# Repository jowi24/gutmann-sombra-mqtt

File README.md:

🇬🇧 **English** · 🇩🇪 [Deutsch](README.de.md)

# gutmann-sombra-mqtt

An ESP8266 board that connects a Gutmann Sombra range hood (cooker hood) to
home automation over Wi-Fi and MQTT, with Home Assistant auto-discovery.
The board sits in the cable between the hood electronics and the front
panel. It reads which front-panel LEDs are lit and can simulate key presses.
The original front panel keeps working as before.

- **Hardware:** KiCad 10 PCB, 80 × 55 mm, through-hole except the ESP-12E
  module, fabrication files included
- **Firmware:** PlatformIO / Arduino, MQTT with Home Assistant discovery,
  OTA updates, Wi-Fi setup portal

## Documentation

| Document | Contents |
|---|---|
| [How the circuit works](docs/CIRCUIT.md) | Beginner-friendly explanation of the hardware: the hood's key matrix, level shifters, power supply, firmware timing, troubleshooting |
| [Hardware design notes](kicad/DESIGN.md) | Part values, sourcing, layout decisions, bring-up findings |
| [Fabrication files](kicad/fab/FAB.md) | Gerber/drill files and PCB order parameters |
| [Operation, diagnostics and flashing](docs/OPERATIONS.md) | Setup, OTA and serial flashing, diagnostics |
| [Changelog](CHANGELOG.md) | Firmware versions |

All documents are also available in German (`*.de.md`).

## Status

- **Hardware:** PCB rev. 0.3, see the [schematic](kicad/schematic.pdf) and
  the [layout](kicad/board-layout.pdf). The fabricated rev. 0.2 boards work
  after a small modification at U3 (diodes + pull-downs, see
  [DESIGN.md](kicad/DESIGN.md)).
- **Firmware:** 0.0.10, PlatformIO, source in [`src/main.cpp`](src/main.cpp).

## Project layout

```
src/main.cpp          firmware
platformio.ini        build configuration (serial and OTA flashing)
docs/                 operation and circuit description
kicad/                schematic, PCB, custom footprint and 3D model
kicad/fab/            fabrication files
fritzing/             2017 perfboard version (reference only)
```

## Building and flashing the firmware

```bash
pio run -e nodemcuv2-ota -t upload
```

This flashes over Wi-Fi (OTA) to `hood-control.local`. For the first flash
or for recovery, use `-e nodemcuv2` via a USB-serial adapter on J2, with
jumper J5 set to FLASH. Details in [OPERATIONS.md](docs/OPERATIONS.md).

## MQTT

All topics live under the configured prefix (default `home/kitchen/hood`).
Home Assistant picks the device up automatically via MQTT discovery
(`homeassistant/…`).

| Topic | Values | Meaning |
|---|---|---|
| `ventilation/state`, `ventilation/set` | `0`–`4` | fan level, `0` = off |
| `light/state`, `light/set` | `true` / `false` | light |
| `timer/state`, `timer/set` | `true` / `false` | run-on timer |
| `maintenance/state` | `true` / `false` | "clean filter" indicator |
| `maintenance/set` | any | resets the filter indicator (6 s key press, only while it is on) |

Diagnostics:

- `diagnostics`: combined JSON status
- `$wifi_rssi`, `$uptime`, `$reset_reason`, `$firmware`, `$ip`, `$last_error`
- `events`: connection events buffered since the last MQTT contact
- `$online`: availability via MQTT last will

## Network

If the stored Wi-Fi network cannot be reached for 20 seconds, the firmware
starts the password-protected hotspot `HoodControl-Setup`. The setup portal
is at `http://192.168.4.1`. The device keeps trying the stored network in
parallel and shuts the hotspot down once the connection is stable.

The blue LED on the ESP module shows the state: fast blinking = connecting
to Wi-Fi, medium = connecting to MQTT, slow = hotspot active, a short flash
every 3 s = all good.

## Background

Blog post about the original 2017 perfboard version (German):
[Do-It-Yourself IoT Modul für die Dunstabzugshaube](https://joachim-wilke.de/blog/2017/12/27/do-it-yourself-iot-modul-fur-die-dunstabzugshaube/)

## License

Copyright (c) 2017–2026 Joachim Wilke. The firmware is open source (MIT). Hardware
and documentation are free for **non-commercial** use only; commercial use (e.g. selling boards, kits or products based on this project)
requires the author's permission.

- **Firmware** (`src/`, `platformio.ini`): [MIT](LICENSE)
- **Hardware and documentation** (`kicad/`, `fritzing/`, `docs/`, Markdown files):
  [CC BY-NC-SA 4.0](LICENSE-HARDWARE-DOCS)

Third-party libraries used by the firmware keep their own licenses.

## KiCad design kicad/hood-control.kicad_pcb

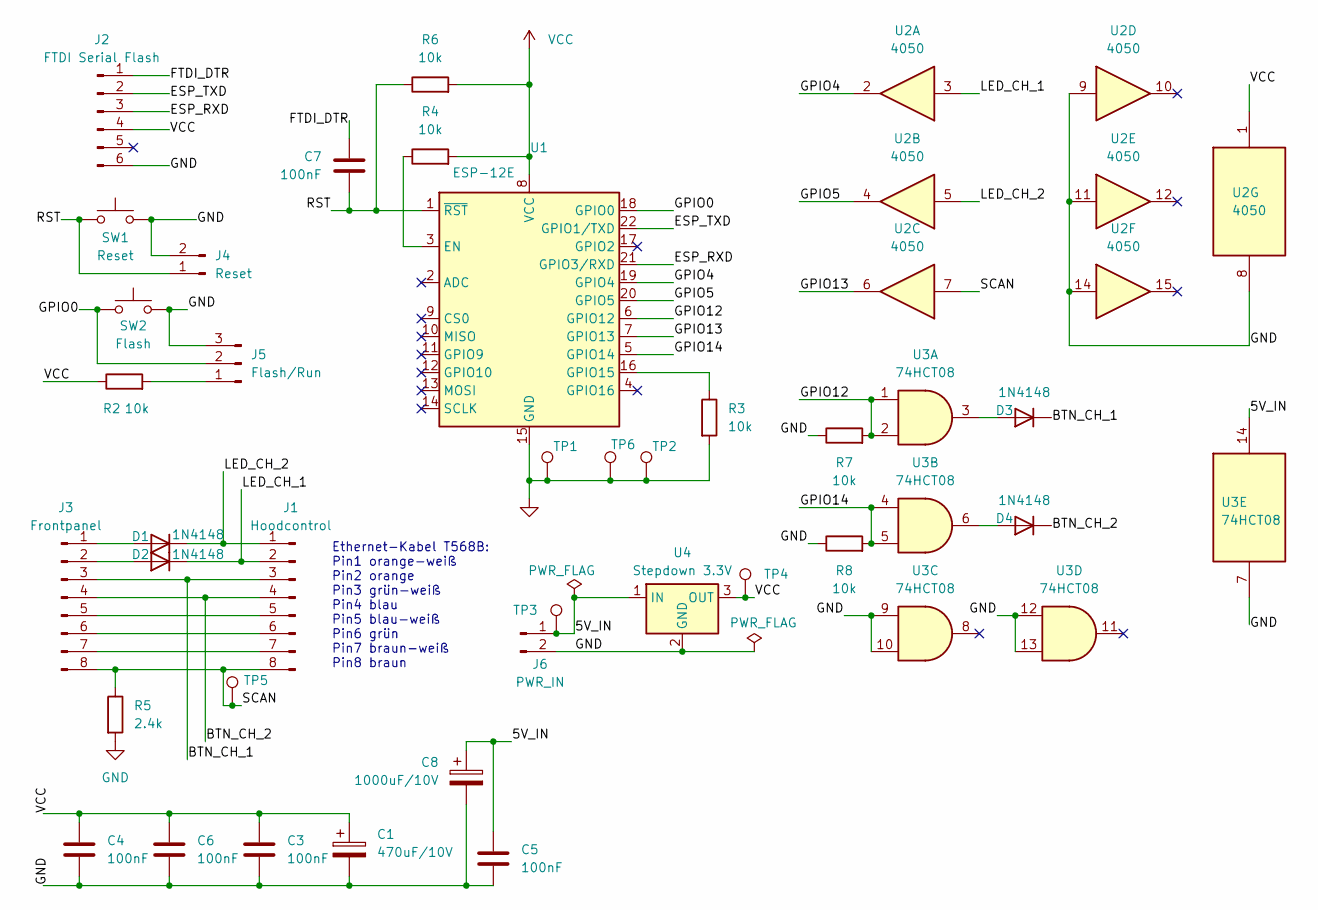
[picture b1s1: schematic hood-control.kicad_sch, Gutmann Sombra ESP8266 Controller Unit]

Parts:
C1: 470uF/10V; CP_Radial_D8.0mm_P3.50mm
C3, C4, C5, C6, C7: 100nF; C_Disc_D5.0mm_W2.5mm_P5.00mm
C8: 1000uF/10V; CP_Radial_D10.0mm_P5.00mm
D1, D2: 1N4148; D_DO-35_SOD27_P7.62mm_Horizontal
D3, D4: 1N4148; D_DO-35_SOD27_P2.54mm_Vertical_AnodeUp
J1: Hoodcontrol; PinHeader_1x08_P2.54mm_Vertical
J2: FTDI Serial Flash; PinHeader_1x06_P2.54mm_Vertical
J3: Frontpanel; PinHeader_1x08_P2.54mm_Vertical
J4: Reset; PinHeader_1x02_P2.54mm_Vertical
J5: Flash/Run; PinHeader_1x03_P2.54mm_Vertical
J6: PWR_IN; PinHeader_1x02_P2.54mm_Vertical
R2, R3, R4, R6: 10k; R_Axial_DIN0207_L6.3mm_D2.5mm_P10.16mm_Horizontal
R5: 2.4k; R_Axial_DIN0207_L6.3mm_D2.5mm_P10.16mm_Horizontal
R7, R8: 10k; R_Axial_DIN0207_L6.3mm_D2.5mm_P2.54mm_Vertical
SW1: Reset; SW_PUSH_6mm
SW2: Flash; SW_PUSH_6mm
TP1, TP2, TP6: GND; TestPoint_THTPad_1.5x1.5mm_Drill0.7mm
TP3: 5V; TestPoint_THTPad_1.5x1.5mm_Drill0.7mm
TP4: 3.3V; TestPoint_THTPad_1.5x1.5mm_Drill0.7mm
TP5: SCAN; TestPoint_THTPad_1.5x1.5mm_Drill0.7mm
U1: ESP-12E
U2: 4050; DIP-16_W7.62mm_Socket
U3: 74HCT08; DIP-14_W7.62mm_Socket
U4: Stepdown 3.3V; TPS63802_Module_25.8x13.0mm

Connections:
/5V_IN: C5.1, C8.1, J6.1, TP3.1 (1_1), U3.14 (VCC), U4.1 (IN)
/BTN_CH_1: D3.1 (K), J1.3, J3.3
/BTN_CH_2: D4.1 (K), J1.4, J3.4
/ESP_RXD: J2.3, U1.21 (GPIO3/RXD)
/ESP_TXD: J2.2, U1.22 (GPIO1/TXD)
/FTDI_DTR: C7.1, J2.1
/GPIO0: J5.2, SW2.1, U1.18 (GPIO0)
/GPIO4: U1.19 (GPIO4), U2.2
/GPIO5: U1.20 (GPIO5), U2.4
/GPIO12: R7.2, U1.6 (GPIO12), U3.1, U3.2
/GPIO13: U1.7 (GPIO13), U2.6
/GPIO14: R8.2, U1.5 (GPIO14), U3.4, U3.5
/LED_CH_1: D2.1 (K), J1.2, U2.3
/LED_CH_2: D1.1 (K), J1.1, U2.5
/RST: C7.2, J4.1, R6.1, SW1.1, U1.1 (~RST)
/SCAN: J1.8, J3.8, R5.1, TP5.1 (1_1), U2.7
GND: C1.2, C3.2, C4.2, C5.2, C6.2, C8.2, J2.6, J4.2, J5.3, J6.2, R3.2, R5.2, R7.1, R8.1, SW1.2, SW2.2, TP1.1 (1_1), TP2.1 (1_1), TP6.1 (1_1), U1.15 (GND), U2.8 (VSS), U2.9, U2.11, U2.14, U3.7 (GND), U3.9, U3.10, U3.12, U3.13, U4.2 (GND)
unnamed: D1.2 (A), J3.1
unnamed: D2.2 (A), J3.2
unnamed: D3.2 (A), U3.3
unnamed: D4.2 (A), U3.6
unnamed: J1.5, J3.5
unnamed: J1.6, J3.6
unnamed: J1.7, J3.7
unnamed: J5.1, R2.2
unnamed: R4.1, U1.3 (EN)
unnamed: R3.1, U1.16 (GPIO15)
VCC: C1.1, C3.1, C4.1, C6.1, J2.4, R2.1, R4.2, R6.2, TP4.1 (1_1), U1.8 (VCC), U2.1 (VCC), U4.3 (OUT)

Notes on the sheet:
Ethernet-Kabel T568B: Pin1 orange-weiß Pin2 orange Pin3 grün-weiß Pin4 blau Pin5 blau-weiß Pin6 grün Pin7 braun-weiß Pin8 braun

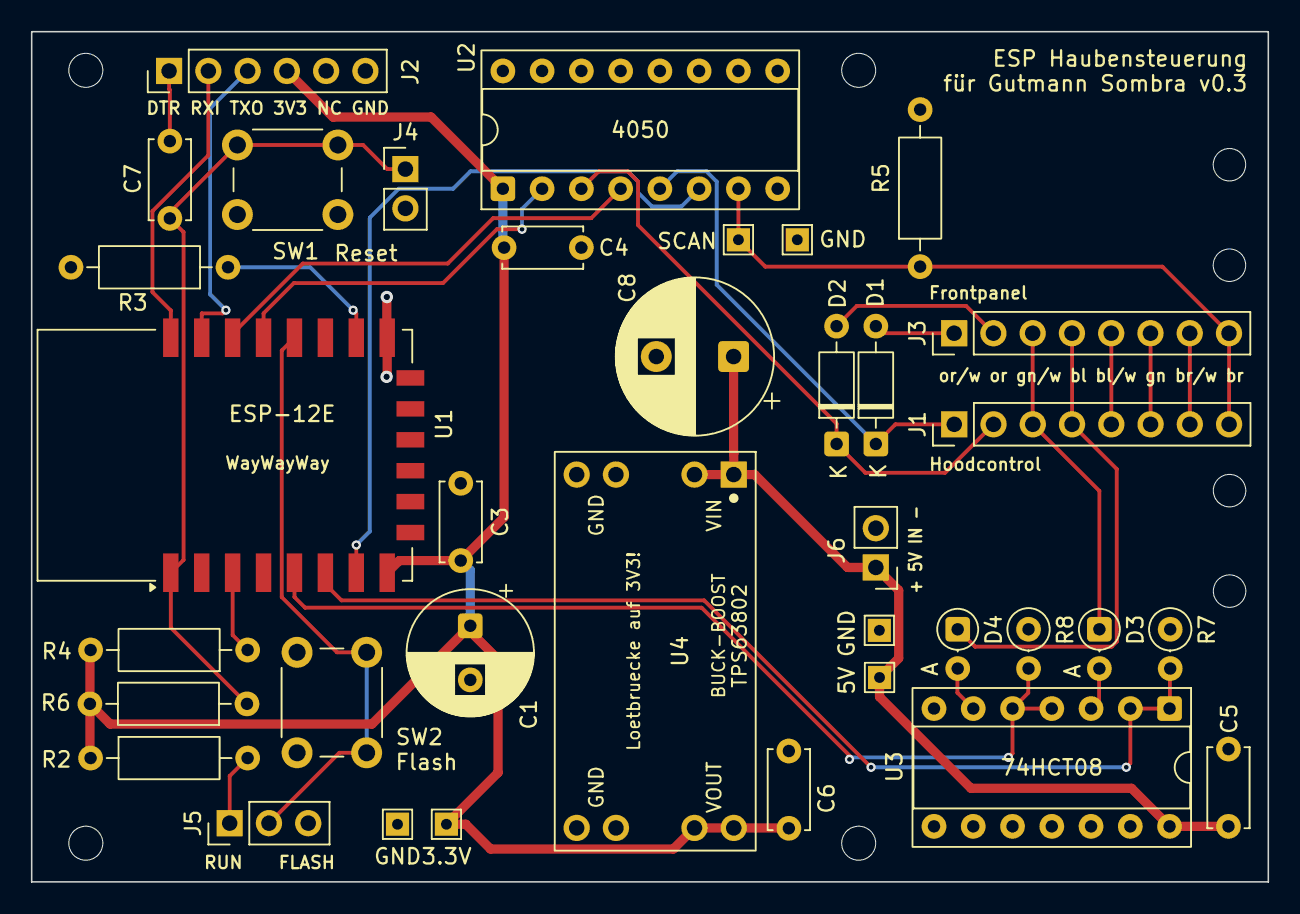
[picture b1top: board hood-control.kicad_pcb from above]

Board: 2 copper layers, 80.0 x 55.0 mm, 44 parts (0 on the bottom side), 28 nets.

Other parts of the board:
H1, H2, H3, H4: MountingHole_2.1mm
MH1, MH2, MH3, MH4: MountingHole_2.2mm_M2

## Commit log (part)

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2017-12-28 Remove debug code
2017-12-28 Add last will, publish uptime, switch to QoS level 1
    - Fixes #1
2017-12-29 Move credentials to separate config file, support OTA password
    - Fixes #4
2017-12-29 Support for maintenance led and button
    - Fixes #2
2018-01-16 Move to IoTBase Lib
    Fixes #6
2018-01-16 Code cleanup
2021-03-30 Migrate to homie
2022-08-12 Add fritzing documents
2026-04-16 Port to PlatformIO v0.0.5: replace Homie with WiFiManager+PubSubClient, add HA MQTT discovery
2026-04-16 Add OTA environment to platformio.ini
2026-04-16 v0.0.5: fan entity for HA discovery, disable ISR during OTA, fan presets 1-4
2026-04-16 v0.0.5: rename device to Abzugshaube, light entity for Haubenlicht
2026-04-16 Add .vscode to .gitignore
